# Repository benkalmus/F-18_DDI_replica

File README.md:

# F-18_DDI_replica
 Replica DDI joystick device using a maple mini development board for STM32F103C8

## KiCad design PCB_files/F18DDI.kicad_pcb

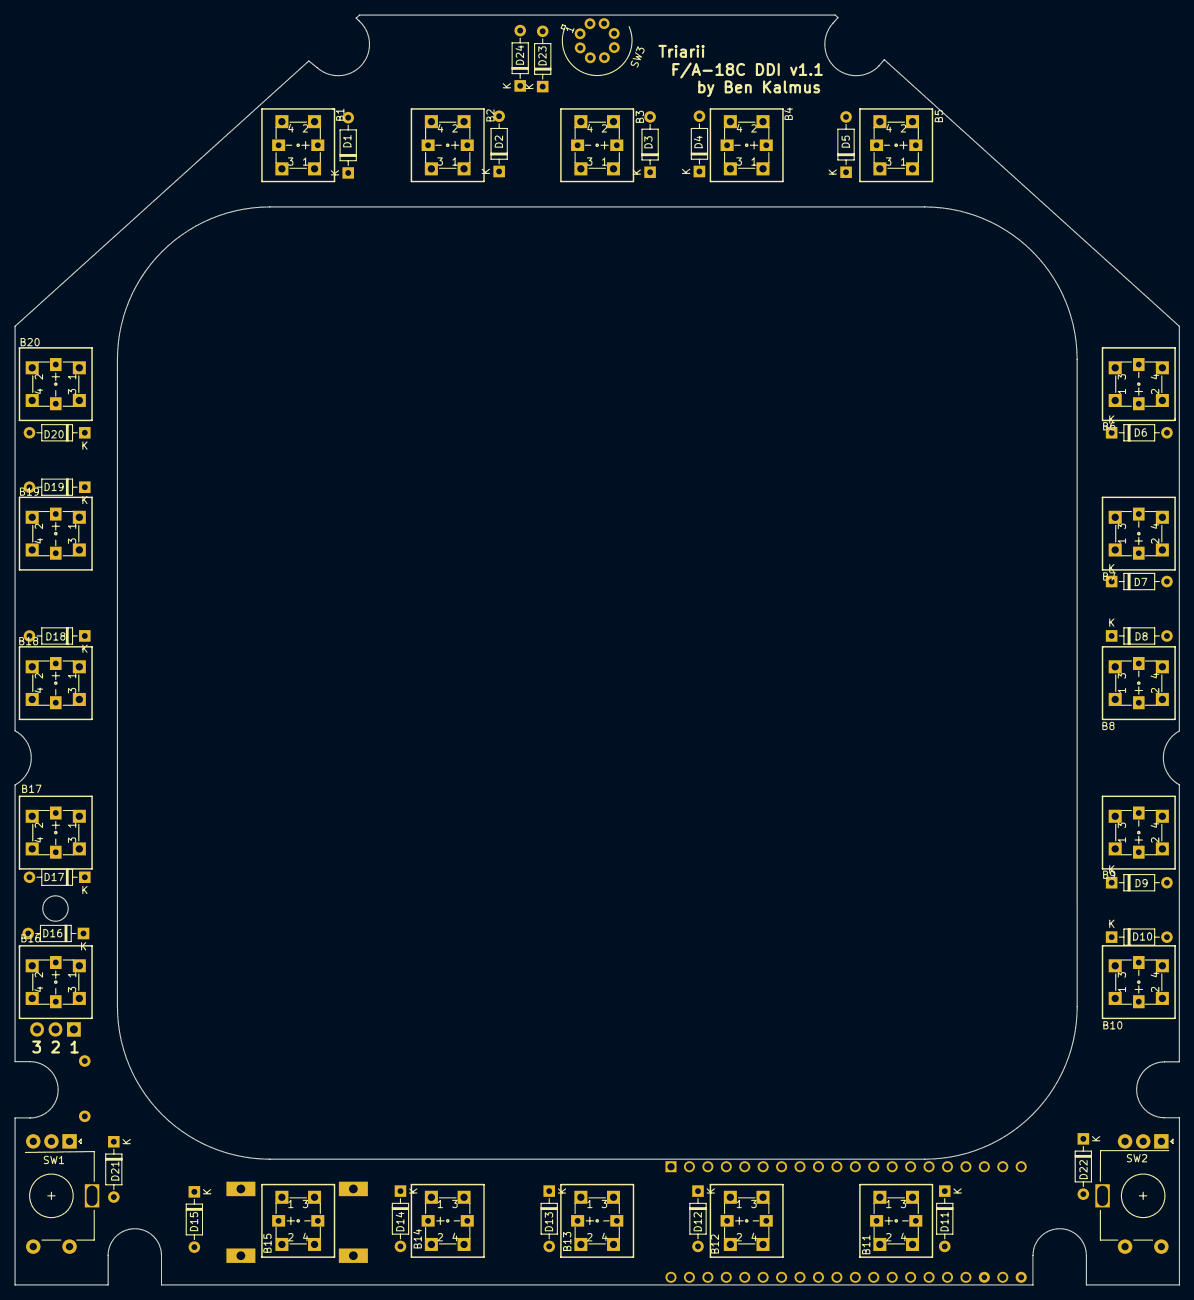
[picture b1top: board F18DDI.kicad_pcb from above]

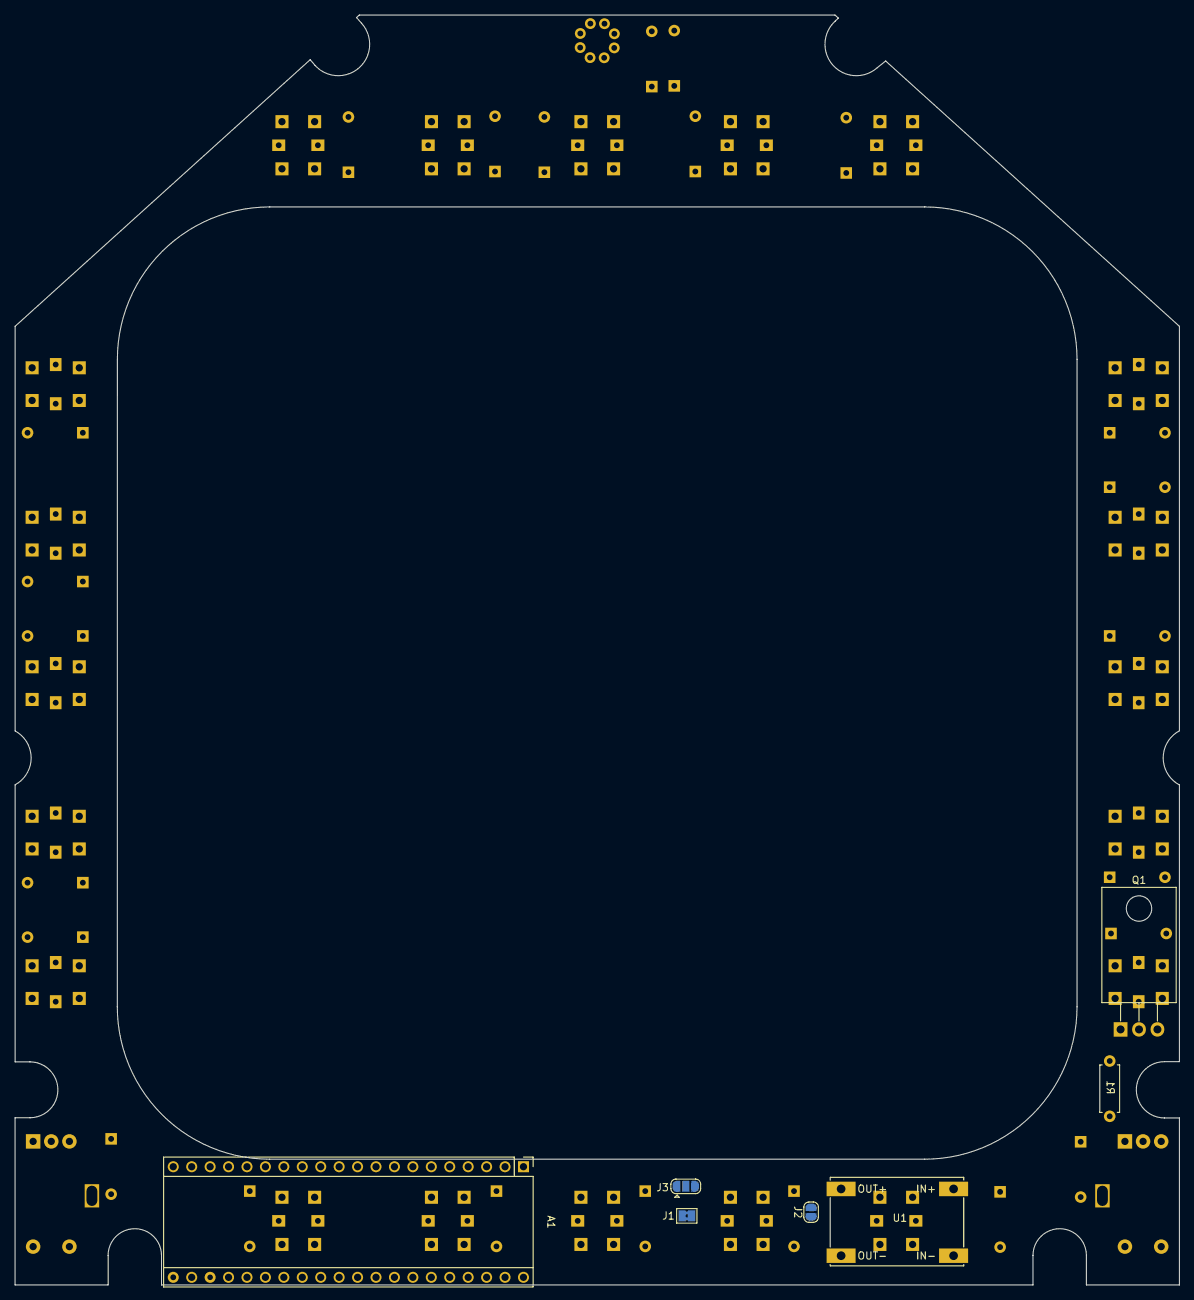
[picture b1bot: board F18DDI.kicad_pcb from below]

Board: 2 copper layers, 160.5 x 175.0 mm, 54 parts (7 on the bottom side), 46 nets, no tracks yet.

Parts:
A1: Maple_Mini
B1, B2, B3, B4, B5, B6, B7, B8, B9, B10, B11, B12, B13, B14, B15, B16, B17, B18, B19, B20: SWLED6_6; SWLED_66
D1, D2, D3, D4, D5, D6, D7, D8, D9, D10, D11, D12, D13, D14, D15, D16, D17, D18, D19, D20, D21, D22, D23, D24: 1N4148; D_DO-35_SOD27_P7.62mm_Horizontal
J1: Conn_01x01; SolderJumper-2_P1.3mm_Bridged2Bar_Pad1.0x1.5mm
J2: Conn_01x02; SolderJumper-2_P1.3mm_Open_RoundedPad1.0x1.5mm
J3: Conn_01x03; SolderJumper-3_P1.3mm_Open_RoundedPad1.0x1.5mm
Q1: IRLB8721PBF; TO-220-3_Horizontal_TabDown
R1: 10k; R_Axial_DIN0207_L6.3mm_D2.5mm_P7.62mm_Horizontal
SW1: Rotary_Encoder_Switch; RotaryEncoder_Alps_EC11E-Switch_Vertical_NoSideFlipped
SW2: Rotary_Encoder_Switch; RotaryEncoder_Alps_EC11E-Switch_Vertical_NoSide
SW3: Lorlin-MTL-21-30; Lorlin_MTL-21-30
U1: STP_DWN_CONV; STEP_DOWN_MINI360

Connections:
/CL0: A1.33, B1.1, B1.2, B2.1, B2.2, B3.1, B3.2, B4.1, B4.2, B5.1, B5.2
/CL1: A1.32, B6.1, B6.2, B7.1, B7.2, B8.1, B8.2, B9.1, B9.2, B10.1, B10.2
/CL2: A1.31, B11.1, B11.2, B12.1, B12.2, B13.1, B13.2, B14.1, B14.2, B15.1, B15.2
/CL3: A1.30, B16.1, B16.2, B17.1, B17.2, B18.1, B18.2, B19.1, B19.2, B20.1, B20.2
/CL4: A1.29, SW1.S1, SW2.S1, SW3.1
/CONV+: B1.5, B2.5, B3.5, B4.5, B5.5, B6.5, B7.5, B8.5, B9.5, B10.5, B11.5, B12.5, B13.5, B14.5, B15.5, B16.5, B17.5, B18.5, B19.5, B20.5, J2.1
/CONV-: B1.6, B2.6, B3.6, B4.6, B5.6, B6.6, B7.6, B8.6, B9.6, B10.6, B11.6, B12.6, B13.6, B14.6, B15.6, B16.6, B17.6, B18.6, B19.6, B20.6, Q1.2
/ENC_A1: A1.17, SW1.A
/ENC_A2: A1.18, SW1.B
/ENC_B1: A1.19, SW2.A
/ENC_B2: A1.20, SW2.B
/GND: A1.2, Q1.3, R1.2, SW1.C, SW2.C, U1.2, U1.4
/LED: A1.16, Q1.1, R1.1
/MAPLE_VIN: A1.21, J3.1
/RW0: A1.22, D1.1, D6.1, D11.1, D16.1, D23.1
/RW1: A1.23, D2.1, D7.1, D12.1, D17.1, D24.1
/RW2: A1.25, D3.1, D8.1, D13.1, D18.1
/RW3: A1.26, D4.1, D9.1, D14.1, D19.1, D21.1
/RW4: A1.27, D5.1, D10.1, D15.1, D20.1, D22.1
/STP_INPUT: J3.2, U1.1
/USB_5V: J1.1, J3.3
unnamed: B1.3, B1.4, D1.2
unnamed: B2.3, B2.4, D2.2
unnamed: B3.3, B3.4, D3.2
unnamed: B4.3, B4.4, D4.2
unnamed: B5.3, B5.4, D5.2
unnamed: B6.3, B6.4, D6.2
unnamed: B7.3, B7.4, D7.2
unnamed: B8.3, B8.4, D8.2
unnamed: B9.3, B9.4, D9.2
unnamed: B10.3, B10.4, D10.2
unnamed: B11.3, B11.4, D11.2
unnamed: B12.3, B12.4, D12.2
unnamed: B13.3, B13.4, D13.2
unnamed: B14.3, B14.4, D14.2
unnamed: B15.3, B15.4, D15.2
unnamed: B16.3, B16.4, D16.2
unnamed: B17.3, B17.4, D17.2
unnamed: B18.3, B18.4, D18.2
unnamed: B19.3, B19.4, D19.2
unnamed: B20.3, B20.4, D20.2
unnamed: D21.2, SW1.S2
unnamed: D22.2, SW2.S2
unnamed: D23.2, SW3.2
unnamed: D24.2, SW3.3
unnamed: J2.2, U1.3

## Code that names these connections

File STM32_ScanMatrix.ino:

/*
Name:       STM32_ScanMatrix.ino
Created:  16/06/2018 13:42:34
Author:     Beniamin Kalmus - TRIARII
*/

#include <USBComposite.h>
#include <USBHID.h>

//#define USE_SERIAL

#define HOW_LONG_HELD_MS	2000

#define ENC_A1	PB14
#define ENC_A2	PB15
#define ENC_B1	PB13
#define ENC_B2	PB12

#define LEDSTRIP	PA8

#define ENC_A_STEP 2
#define ENC_B_STEP 2

#define OSD_BTNS	22

#define ROT_SWITCH_JOY_0		1+OSD_BTNS
#define ROT_SWITCH_JOY_1		2+OSD_BTNS
#define ROT_SWITCH_JOY_2		3+OSD_BTNS

#define ENC_SWITCH_JOY_A_CW		5+OSD_BTNS
#define ENC_SWITCH_JOY_A_CCW	4+OSD_BTNS
#define ENC_SWITCH_JOY_B_CW		7+OSD_BTNS
#define ENC_SWITCH_JOY_B_CCW	6+OSD_BTNS

#define ENC_A_PUSH				21
#define ENC_B_PUSH				22

//Driven outputs	//{ PA0, PA1, PA2, PA3, PA4 };       {PA1 ,PA4, PA3, PA2,PA0, }
uint16_t columnPins[] = { PA0, PA1, PA2, PA3, PA4 };
//uint16_t columnPins[] = { PA1 ,PA4, PA3, PA2,PA0, };


//Input PullDowns		 { PB11, PB10, PB0, PA7, PA6 };		 { PB10 ,PA7 ,  PB11, PB0, PA6 }
//uint16_t rowPins[] = { PA6, PA7, PB0, PB10, PB11 };
uint16_t rowPins[] = { PB11, PB10, PB0, PA7, PA6 };


int num_cols = sizeof(columnPins) / sizeof(uint16_t);
int num_rows= sizeof(rowPins) / sizeof(uint16_t);

uint16_t LED_Brightness = 65535;

int8 encA_steps = 0, encB_steps =0 ;
int16_t encoderPosA = 0, encoderPosB = 0;
uint8_t moveAmount = (uint8_t)(1024/40);
uint32_t joySend = 0, joyInterval = 10000;

int32_t encA_time = 0, encB_time = 0;
uint16_t push_Time = 300; //hold time in ms
uint8_t encA_state = 0, prevStateA = 0;
uint32_t hold_encA_time = 0;

uint8_t encB_state = 0, prevStateB = 0;

static uint8_t old_A = 0;
static uint8_t old_B = 0;

void interruptEncoderA()
{
	int8 val = read_encoder(ENC_A1, ENC_A2, & old_A);
	if (val == 1)	// if output is not 0, valid
	{

		encA_steps++;
		if (encA_steps >= ENC_A_STEP) 
		{
			encA_steps = 0;
			//only change the joystick value if the led brightness is not being changed
			encoderPosA += moveAmount;
			if (encoderPosA > 1023) encoderPosA = 1023;
#if !defined(USE_SERIAL)
			if (!encA_state) Joystick.button(ENC_SWITCH_JOY_A_CW, 1);
#endif
		}
	}
	else if (val == -1)
	{
		encA_steps--;
		if (encA_steps <= (-1 * ENC_A_STEP))
		{
			encA_steps = 0;
			//only change the joystick value if the led brightness is not being changed
			encoderPosA -= moveAmount;
			if (encoderPosA < 0) encoderPosA = 0;
#if !defined(USE_SERIAL)
			if (!encA_state) Joystick.button( ENC_SWITCH_JOY_A_CCW, 1);
#endif
		}
	}
	if (!encA_state)	Joystick.Xrotate((uint16_t)encoderPosA);
	else
	{
		LED_Brightness = encoderPosA;
		hold_encA_time = millis();
	}
}

void interruptEncoderB()
{
	int8 val = read_encoder(ENC_B1, ENC_B2, & old_B);
	if (val == 1)	// if output is not 0, valid
	{

		encB_steps++;
		if (encB_steps >= ENC_B_STEP)
		{
			encB_steps = 0;
			encoderPosB += moveAmount;
			if (encoderPosB > 1023) encoderPosB = 1023;
#if !defined(USE_SERIAL)
			Joystick.button(ENC_SWITCH_JOY_B_CW, 1);
#endif
		}
	}
	else if (val == -1)
	{
		encB_steps--;
		if (encB_steps <= (-1 * ENC_B_STEP))
		{
			encB_steps = 0;
			encoderPosB -= moveAmount;
			if (encoderPosB < 0) encoderPosB = 0;
#if !defined(USE_SERIAL)
			Joystick.button(ENC_SWITCH_JOY_B_CCW, 1);
#endif
		}
	}
	Joystick.Yrotate((uint16_t)encoderPosB);

}

int8_t read_encoder(uint8 pin1, uint8 pin0, uint8_t *prev_state)
{
	static int8_t enc_states[] = { 0,-1,1,0,1,0,0,-1,-1,0,0,1,0,1,-1,0 };
	*prev_state <<= 2;	//remember previous state
	//							possible states: 0b00, 0b01, 0b10, 0b11
	uint8_t encoder_combined = digitalRead(pin1) << 1 | (digitalRead(pin0));
	*prev_state |= (encoder_combined & 0b00000011);		//adds current states of pins a1, a2 to the least signif. bits, and leaving the rest 0 so that it can be ORed with ol_AB
	
	return (enc_states[(*prev_state & 0x0f)]);
}


// The setup() function runs once each time the micro-controller starts
void setup()
{
#if !defined(USE_SERIAL)
	USBHID.begin(HID_JOYSTICK,41,42,"Triarii Electronics", "Hornet DDI");
#endif
	pinMode(33, OUTPUT);	//default inbuilt led
	digitalWrite(33, 0);	// set to low
	for (int i = 0; i < num_cols; i++)
	{
		pinMode(columnPins[i], OUTPUT); //using push pull resistors
	}
	for (int i = 0; i < num_rows; i++)
	{
		pinMode(rowPins[i], INPUT_PULLDOWN);  //rows need to be pulled down to read a digital 0 when off.
	}

	pinMode(LEDSTRIP, PWM);
	//digitalWrite(LEDSTRIP, 1);
	//encoder
	pinMode(ENC_A1, INPUT_PULLUP);
	pinMode(ENC_A2, INPUT_PULLUP);
	pinMode(ENC_B1, INPUT_PULLUP);
	pinMode(ENC_B2, INPUT_PULLUP);
	attachInterrupt(ENC_A1, interruptEncoderA, CHANGE);
	attachInterrupt(ENC_A2, interruptEncoderA, CHANGE);
	attachInterrupt(ENC_B1, interruptEncoderB, CHANGE);
	attachInterrupt(ENC_B2, interruptEncoderB, CHANGE);

#if defined (USE_SERIAL)
	Serial.begin(115200);
	while (!Serial);    //wait for seria
	Serial.println("Connected");

	Serial.print("Rows ");
	Serial.println(num_rows);
	Serial.print("Cols ");
	Serial.println(num_cols);
#endif
#if !defined(USE_SERIAL)
	Joystick.setManualReportMode(true); // aggregate data before sending
	delay(1000);
	//reset all axes
	Joystick.Xrotate(0);
	Joystick.Yrotate(0);
	for (int i = 0; i < 32; i++)
	{
		Joystick.button(i, 0);
	}
	Joystick.send();
#endif
}

// Add the main program code into the continuous loop() function
void loop()
{
	delay(5); //crude debounce

	uint32 //ledFadeValue = map(encoderPosB, 0, 1023, 0, 65535);		//linear mapping - bad
	ledFadeValue = (uint32_t)pow(2.718, (float)LED_Brightness / 92.11f);		//using e to get a better response curve.
	//sigmoid
	//ledFadeValue =( 65535 / (1 + (pow(2.718, -(encoderPosA-512)/80))));

	if (ledFadeValue > 65535) ledFadeValue = 65535;

	if (encA_state == 1)	pwmWrite(LEDSTRIP, ledFadeValue);

	if (millis() - hold_encA_time >= HOW_LONG_HELD_MS)
	{
		//hold_encA_time = millis();
		//stops changing the led brightness
		encA_state = 0;	//reset state back to 0, in case user forgets to push the encoder btn down again.
	}
	
	
	digitalWrite(columnPins[4], 1);		//set last column to 1
	for (int j = 0; j < num_rows; j++)
	{
#if !defined(USE_SERIAL)
		if (digitalRead(rowPins[0]))
		{
			Joystick.button( ROT_SWITCH_JOY_1, 1);
			Joystick.button( ROT_SWITCH_JOY_0, 0);
			Joystick.button( ROT_SWITCH_JOY_2, 0);
		}
		else if (digitalRead(rowPins[1]))
		{
			Joystick.button( ROT_SWITCH_JOY_2, 1);
			Joystick.button( ROT_SWITCH_JOY_0, 0);
			Joystick.button( ROT_SWITCH_JOY_1, 0);
		}
		else
		{
			Joystick.button( ROT_SWITCH_JOY_0, 1);
			Joystick.button(ROT_SWITCH_JOY_1, 0);
			Joystick.button(ROT_SWITCH_JOY_2, 0);
		}
#endif
		
	
		if (!digitalRead(rowPins[3]))
		{
			prevStateA = 0;
			Joystick.button(ENC_A_PUSH, 0);
		}
		else	Joystick.button(ENC_A_PUSH, 1 );

		if (!digitalRead(rowPins[4]))
		{
			prevStateB = 0;
			Joystick.button(ENC_B_PUSH, 0);
		}
		else	Joystick.button(ENC_B_PUSH, 1);

		//check if encoder push down buttons are pressed or held
		if (digitalRead(rowPins[3]) && prevStateA == 0)
		{
			encA_time = millis();			//note the time pressed
			prevStateA = 1;
		}
		else if (digitalRead(rowPins[3]) && prevStateA == 1 && ((int32_t)millis() - encA_time > push_Time))
		{
			encA_state ^= 1;
			if (encA_state == 1) 
			{
				hold_encA_time = millis();
			}
			encA_time = millis() + 100000;		//prevents the if statement from being executed repeatedly.
		}
	}
	digitalWrite(columnPins[4], 0);
	delay(5);

	//SCAN MATRIX for the OSD BUTTONS
	for (int i = 0; i < 4; i++)
	{
		digitalWrite(columnPins[i], 1);
		for (int j = 0; j < num_rows; j++)
		{
			//check if current pin is HIGH
			if (digitalRead(rowPins[j]))
			{
				//buttons start at 1...
				//to get button id: column number *(rows connected per column) + row number + 1
#if !defined(USE_SERIAL)
				Joystick.button((i*5) + j+1, 1);
#endif
			}
			else
			{
#if !defined(USE_SERIAL)
				Joystick.button((i * 5) + j + 1, 0);
#endif
			}
		}
		//switch the pin off for the next loop
		digitalWrite(columnPins[i], 0);
		delay(1);		//1ms delay to wait for the pin to be brought down fully
	}

#if !defined(USE_SERIAL)
	if (micros() - joySend > joyInterval)	//sends data at specific intervals
	{
		joySend = micros();
		Joystick.send();		//sends data buffer
		Joystick.button(ENC_SWITCH_JOY_A_CW, 0);	//switch off rotary encoder buttons
		Joystick.button( ENC_SWITCH_JOY_A_CCW, 0);
		Joystick.button( ENC_SWITCH_JOY_B_CW, 0);
		Joystick.button( ENC_SWITCH_JOY_B_CCW, 0);
	}
#endif
}

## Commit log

2021-01-14 add files
2021-01-14 Added PCB (kicad) files
